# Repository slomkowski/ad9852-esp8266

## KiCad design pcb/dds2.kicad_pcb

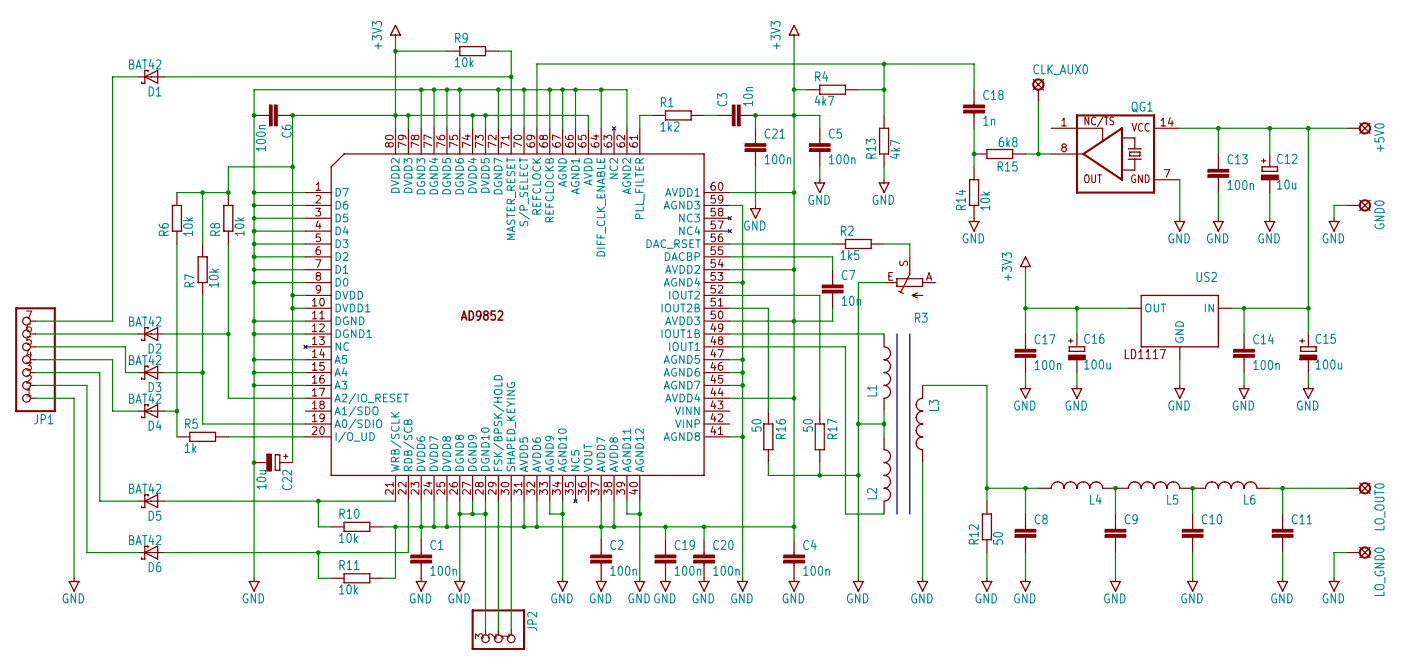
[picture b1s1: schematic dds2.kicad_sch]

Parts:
+5V0: LSP10
C1, C2, C4, C5, C6, C19, C20, C21: 100n; C0805K
C3, C7: 10n; C0805K
C8, C9, C10, C11: C-EU025-030X050; C025-030X050
C12, C22: 10u; B45181A
C13, C14, C17: 100n; C050-035X075
C15, C16: 100u; B45181B
C18: 1n; C025-030X050
CLK_AUX0: LSP10
D1, D2, D3, D4, D5, D6: BAT42; DO35-10
GND0: LSP10
JP1: PINHD-1X7; 1X07
JP2: PINHD-1X3; 1X03
L1, L2, L3, L4, L5, L6: L-US0204/5; 0204_5
LO_GND0: LSP10
LO_OUT0: LSP10
QG1: XO-14; DIL14S
R1: 1k2; R1210
R2: 1k5; 0207_12
R3: TRIM_EU-CA6H; CA6H
R4, R13: 4k7; 0207_12
R5: 1k; 0207_12
R6, R7, R8, R9, R10, R11, R14: 10k; 0207_12
R12, R16, R17: 50; 0207_12
R15: 6k8; 0207_12
U$1: AD9852; SQ-80
US2: LD1117; TO-220

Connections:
GND: C1.2, C2.2, C4.2, C5.2, C6.2, C8.2, C9.2, C10.2, C11.2, C12.-, C13.2, C14.2, C15.-, C16.-, C17.2, C19.2, C20.2, C21.2, C22.-, GND0.MP, JP1.1, JP2.3, L1.2, L2.1, L3.1, LO_GND0.MP, QG1.7 (GND), R3.E, R12.1, R13.1, R14.1, R16.2, R17.2, U$1.1 (D7), U$1.2 (D6), U$1.3 (D5), U$1.4 (D4), U$1.5 (D3), U$1.6 (D2), U$1.7 (D1), U$1.8 (D0), U$1.11 (DGND), U$1.12 (DGND1), U$1.14 (A5), U$1.15 (A4), U$1.16 (A3), U$1.26 (DGND8), U$1.27 (DGND9), U$1.28 (DGND10), U$1.33 (AGND9), U$1.34 (AGND10), U$1.39 (AGND11), U$1.40 (AGND12), U$1.41 (AGND8), U$1.45 (AGND7), U$1.46 (AGND6), U$1.47 (AGND5), U$1.53 (AGND4), U$1.59 (AGND3), U$1.62 (AGND2), U$1.64 (DIFF_CLK_ENABLE), U$1.66 (AGND1), U$1.67 (AGND), U$1.68 (REFCLOCKB), U$1.70 (S/P_SELECT), U$1.72 (DGND7), U$1.75 (DGND6), U$1.76 (DGND5), U$1.77 (DGND4), U$1.78 (DGND3), US2.1 (GND)
unnamed: C7.1, U$1.55 (DACBP)
unnamed: L1.1, U$1.49 (IOUT1B)
unnamed: L2.2, U$1.48 (IOUT1)
unnamed: R2.1, U$1.56 (DAC_RSET)
unnamed: C3.1, R1.2
unnamed: R1.1, U$1.61 (PLL_FILTER)
unnamed: R2.2, R3.S
unnamed: R5.2, U$1.20 (I/O_UD)
unnamed: D1.A, R9.2, U$1.71 (MASTER_RESET)
unnamed: D5.A, R10.1, U$1.21 (WRB/SCLK)
unnamed: D6.A, R11.1, U$1.22 (RDB/SCB)
unnamed: D2.A, R8.1, U$1.17 (A2/IO_RESET)
unnamed: D3.A, R7.1, U$1.19 (A0/SDIO)
unnamed: D4.A, R5.1, R6.1
unnamed: C8.1, L3.2, L4.1, R12.2
unnamed: D1.C, JP1.7
unnamed: D2.C, JP1.6
unnamed: D3.C, JP1.5
unnamed: D4.C, JP1.4
unnamed: D5.C, JP1.3
unnamed: D6.C, JP1.2
unnamed: JP2.1, U$1.30 (SHAPED_KEYING)
unnamed: JP2.2, U$1.29 (FSK/BPSK/HOLD)
unnamed: C9.1, L4.2, L5.1
unnamed: C10.1, L5.2, L6.1
unnamed: C11.1, L6.2, LO_OUT0.MP
unnamed: +5V0.MP, C12.+, C13.1, C14.1, C15.+, QG1.14 (VCC), US2.3 (IN)
unnamed: C18.1, R4.2, R13.2, U$1.69 (REFCLOCK)
unnamed: C18.2, R14.2, R15.2
unnamed: CLK_AUX0.MP, QG1.8 (OUT), R15.1
unnamed: R16.1, U$1.51 (IOUT2B)
unnamed: R17.1, U$1.52 (IOUT2)
unnamed: C1.1, C2.1, C3.2, C4.1, C5.1, C6.1, C7.2, C16.+, C17.1, C19.1, C20.1, C21.1, C22.+, R4.1, R6.2, R7.2, R8.2, R9.1, R10.2, R11.2, U$1.9 (DVDD), U$1.10 (DVDD1), U$1.23 (DVDD6), U$1.24 (DVDD7), U$1.25 (DVDD8), U$1.31 (AVDD5), U$1.32 (AVDD6), U$1.37 (AVDD7), U$1.38 (AVDD8), U$1.44 (AVDD4), U$1.50 (AVDD3), U$1.54 (AVDD2), U$1.60 (AVDD1), U$1.65 (AVDD), U$1.73 (DVDD5), U$1.74 (DVDD4), U$1.79 (DVDD3), U$1.80 (DVDD2), US2.2 (OUT)

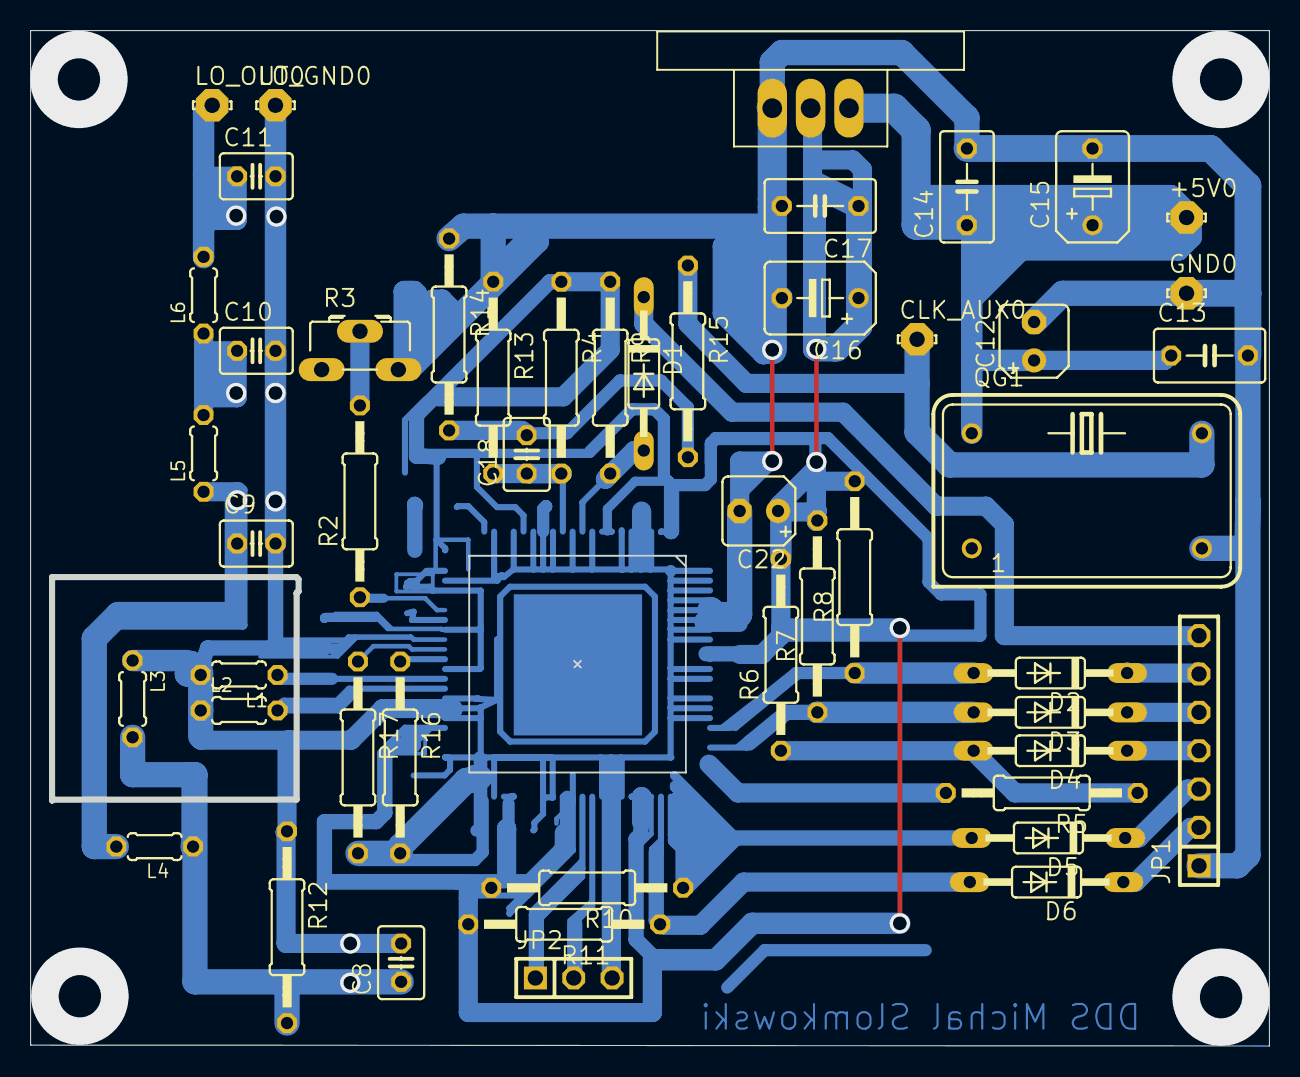
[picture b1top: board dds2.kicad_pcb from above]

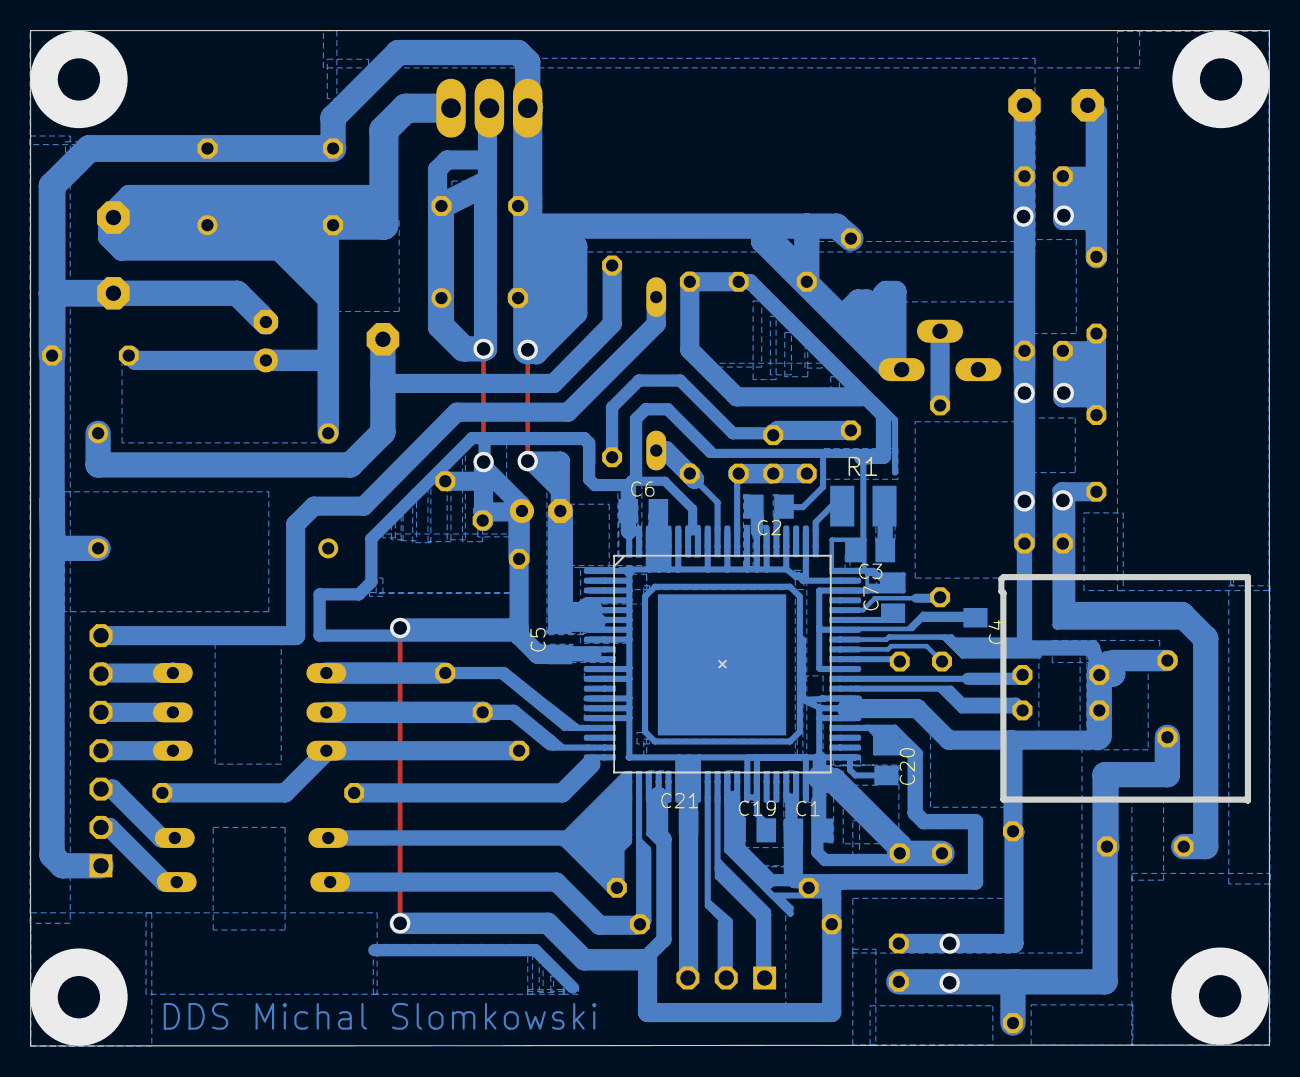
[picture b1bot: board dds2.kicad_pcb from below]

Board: 2 copper layers, 82.0 x 67.2 mm, 61 parts (11 on the bottom side), 34 nets.
